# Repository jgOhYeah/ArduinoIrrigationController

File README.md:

# Arduino Irrigation Controller
An irrigation controller for a small farm that remotely controls a set of linear actuators that raise and lower flaps over pipes.
## This is still a WORK IN PROGRESS!
I am mainly using this repository to transfer files! If you are interested in using this, have a look at `SlaveUnit/SlaveUnit3.6` and `Controller/3.4`. **There will be bugs!**
## Links
Most of these notes are very out of date and based off old versions - I have not properly updated the documentation for quite a while!
- [User Guide](Documentation/UserGuide.md)
- [Technical Notes and rambling](Documentation/TechnicalNotes)
# Parts
## Master
- Arduino Mega
- 3 buttons (left, right and select)
- Character lcd (currently using a 40 by 2 lcd, also works on a 16 by 2 lcd by selecting macros and `#defines`, could be modified for a 20 by 4).
## Slaves
- Arduino Uno / Nano / Atmega328p driving a H bridge motor driver to power a linear actuator opening and shutting the bay outlets

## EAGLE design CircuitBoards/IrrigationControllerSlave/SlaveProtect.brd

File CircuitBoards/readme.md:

Please note that these are a work in progress.

The slave circuit and layout is about done, I am waiting to finish the slave design and build several of them to test lots of devices on the bus before I do the master board layout.

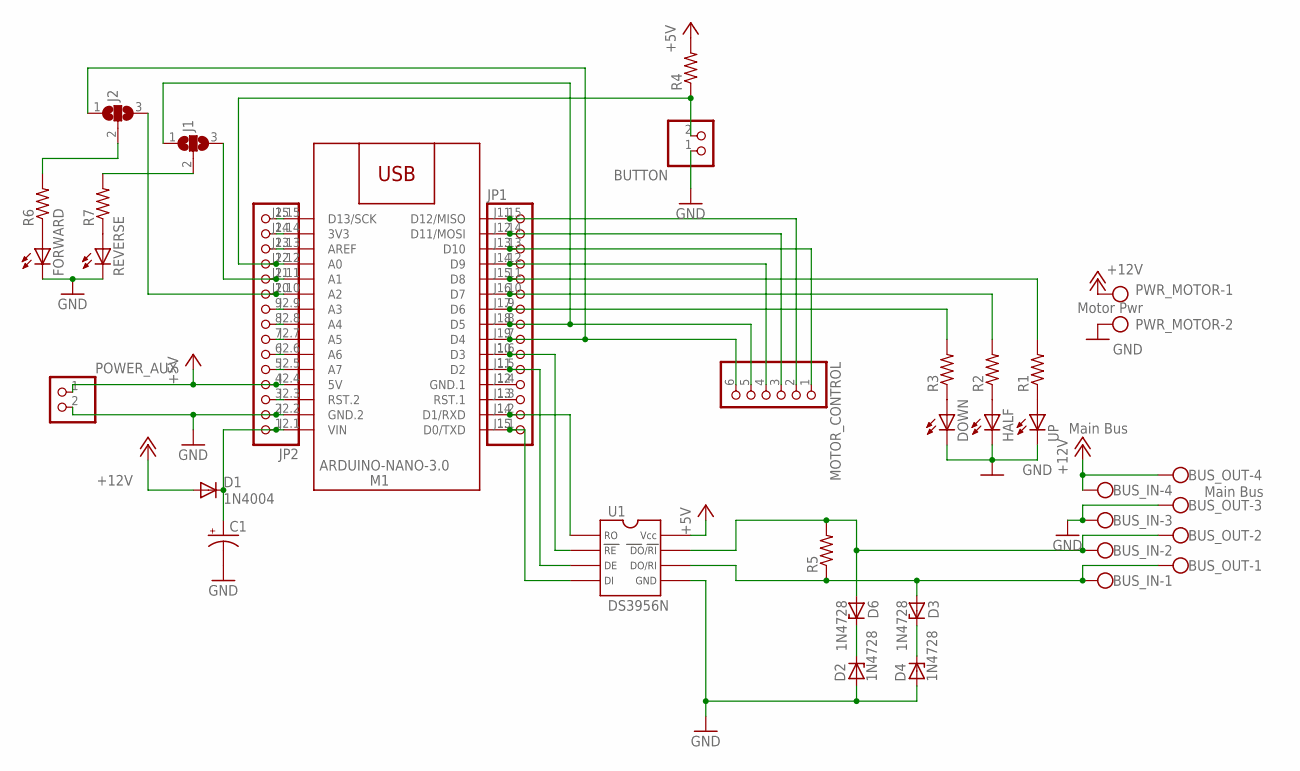
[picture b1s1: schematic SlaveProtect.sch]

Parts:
BUS_IN: Main Bus; W237-4
BUS_OUT: Main Bus; W237-4
BUTTON: PINHD-1X2; 1X02
C1: CPOL-USE3.5-10; E3,5-10
D1: 1N4004; DO41-10
D2, D3, D4, D6: 1N4728; DO41Z10
DOWN: LED5MM
FORWARD: LED5MM
HALF: LED5MM
J1, J2: SJ2W; SJ_2
JP1, JP2: PINHD-1X15-CB; 1X15-CB
M1: ARDUINO-NANO-3.0
MOTOR_CONTROL: PINHD-1X6; 1X06
POWER_AUX: PINHD-1X2; 1X02
PWR_MOTOR: Motor Pwr; W237-102
R1, R2, R3, R4, R5, R6, R7: FLIPFLOP-RES; 0805-THM
REVERSE: LED5MM
U1: DS3956N; DIL08
UP: LED5MM

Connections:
+5V: JP2.4, M1.J2.4 (5V), POWER_AUX.1, R4.2, U1.8 (VCC)
+12V: BUS_IN.4, BUS_OUT.4, D1.A, PWR_MOTOR.1
GND: BUS_IN.3, BUS_OUT.3, BUTTON.1, C1.-, D2.A, D4.A, DOWN.K (C), FORWARD.K (C), HALF.K (C), JP2.2, M1.J2.2 (GND.2), POWER_AUX.2, PWR_MOTOR.2, REVERSE.K (C), U1.5 (GND), UP.K (C)
unnamed: R1.1, UP.A
unnamed: HALF.A, R2.1
unnamed: DOWN.A, R3.1
unnamed: BUTTON.2, JP2.12, M1.J2.12 (A0), R4.1
unnamed: BUS_IN.1, BUS_OUT.1, D3.A, R5.1, U1.6 (DO/RI)
unnamed: BUS_IN.2, BUS_OUT.2, D6.A, R5.2, U1.7 (_DO/RI_)
unnamed: JP1.10, M1.J1.6 (D3), U1.2 (_RE_)
unnamed: JP1.11, M1.J1.5 (D2), U1.3 (DE)
unnamed: JP1.14, M1.J1.2 (D1/RXD), U1.1 (RO)
unnamed: JP1.15, M1.J1.1 (D0/TXD), U1.4 (DI)
unnamed: JP1.7, M1.J1.9 (D6), R3.2
unnamed: JP1.6, M1.J1.10 (D7), R2.2
unnamed: JP1.5, M1.J1.11 (D8), R1.2
unnamed: J1.1, JP1.8, M1.J1.8 (D5), MOTOR_CONTROL.5
unnamed: J1.2, R7.2
unnamed: C1.+, D1.C, JP2.1, M1.J2.1 (VIN)
unnamed: FORWARD.A, R6.1
unnamed: R7.1, REVERSE.A
unnamed: D2.C, D6.C
unnamed: D3.C, D4.C
unnamed: JP2.3, M1.J2.3 (RST.2)
unnamed: JP2.5, M1.J2.5 (A7)
unnamed: JP2.6, M1.J2.6 (A6)
unnamed: JP2.7, M1.J2.7 (A5)
unnamed: JP2.8, M1.J2.8 (A4)
unnamed: JP2.9, M1.J2.9 (A3)
unnamed: J2.3, JP2.10, M1.J2.10 (A2)
unnamed: J1.3, JP2.11, M1.J2.11 (A1)
unnamed: J2.1, JP1.9, M1.J1.7 (D4), MOTOR_CONTROL.6
unnamed: JP2.13, M1.J2.13 (AREF)
unnamed: JP2.14, M1.J2.14 (3V3)
unnamed: JP2.15, M1.J2.15 (D13/SCK)
unnamed: JP1.1, M1.J1.15 (D12/MISO), MOTOR_CONTROL.2
unnamed: JP1.2, M1.J1.14 (D11/MOSI), MOTOR_CONTROL.3
unnamed: JP1.3, M1.J1.13 (D10), MOTOR_CONTROL.1
unnamed: JP1.12, M1.J1.4 (GND.1)
unnamed: JP1.13, M1.J1.3 (RST.1)
unnamed: JP1.4, M1.J1.12 (D9), MOTOR_CONTROL.4
unnamed: J2.2, R6.2

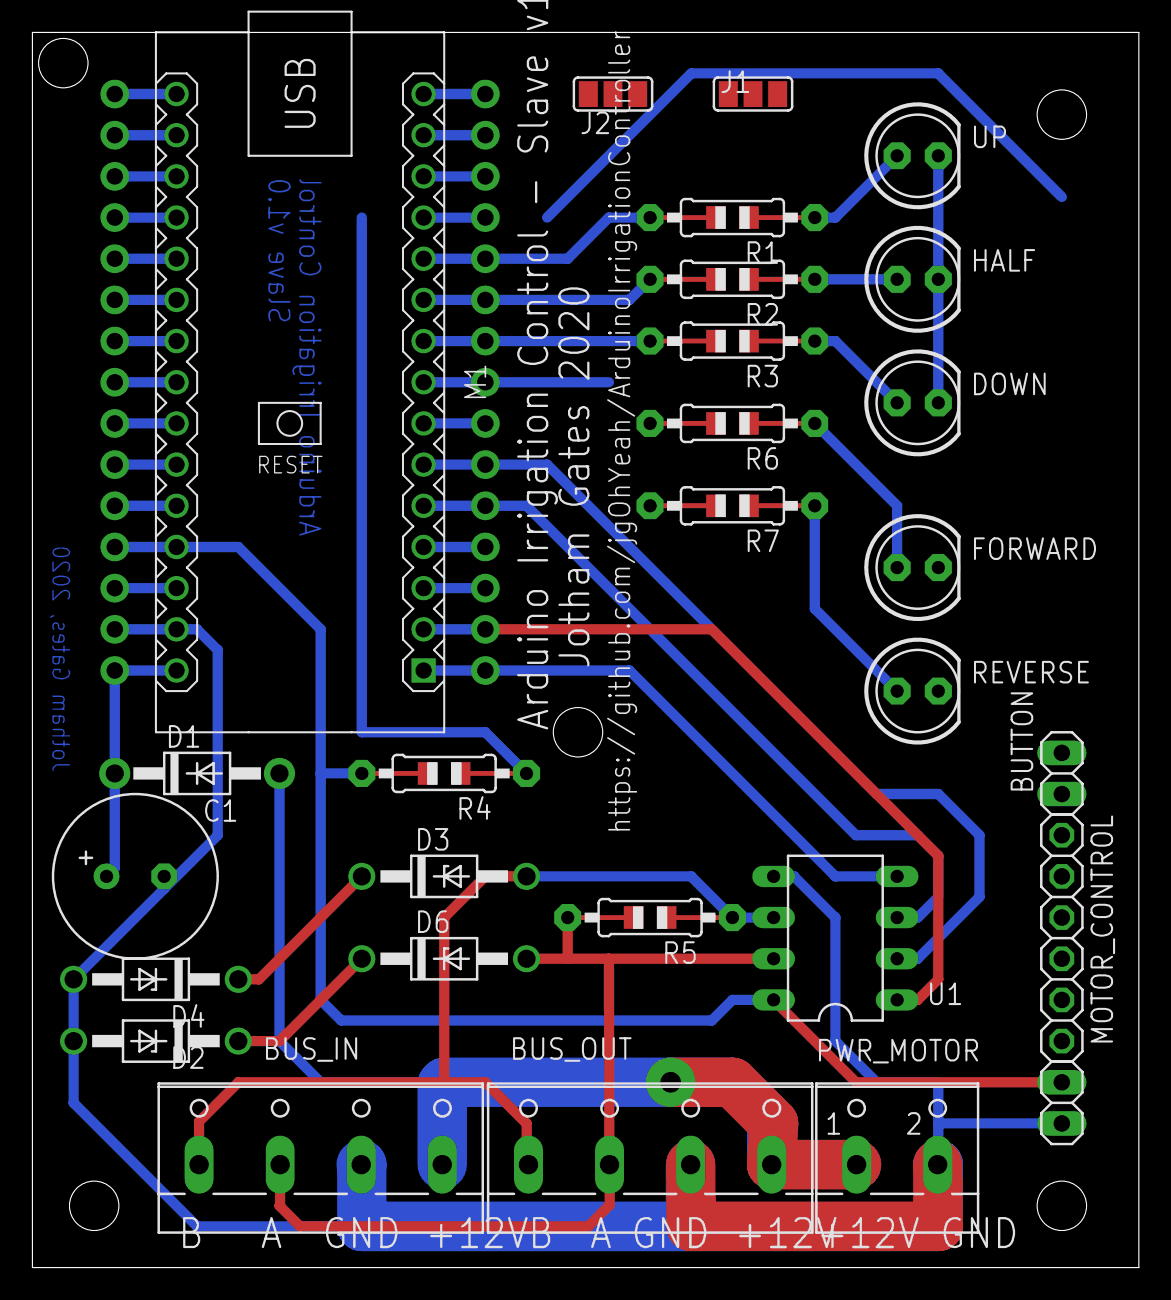
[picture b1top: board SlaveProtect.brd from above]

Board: 2 copper layers, 68.2 x 76.2 mm, 30 parts (0 on the bottom side), 42 nets.

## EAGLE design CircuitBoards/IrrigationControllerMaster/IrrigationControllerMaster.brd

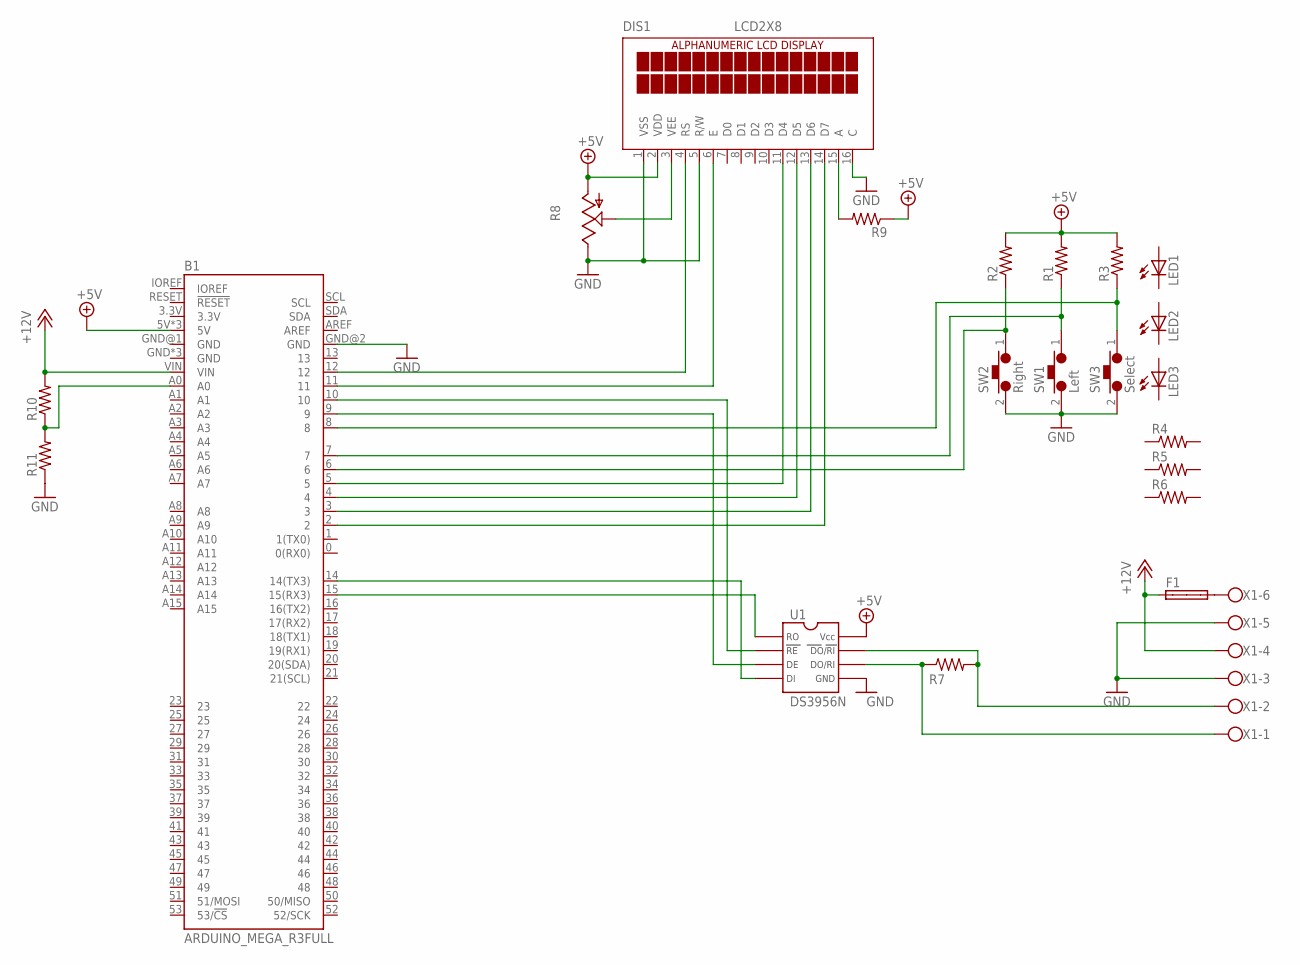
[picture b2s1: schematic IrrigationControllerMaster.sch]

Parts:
B1: ARDUINO_MEGA_R3FULL; ARDUINO_MEGA_NO_SILK
DIS1: LCD2X8; 2X08_JAYCAR
F1: SHK20L
LED1, LED2, LED3: LED5MM
R1, R2, R3, R4, R5, R6, R7, R9, R10, R11: FLIPFLOP-RES; 0805-THM
R8: TRIM_US-ECP10S; ECP10S
SW1: Left; 2PIN
SW2: Right; 2PIN
SW3: Select; 2PIN
U1: DS3956N; DIL08
X1: W237-6

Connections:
+5V: B1.5V, B1.5V@1 (5V), B1.5V@2 (5V), DIS1.2 (VDD), R1.2, R2.2, R3.2, R8.A, R9.1, U1.8 (VCC)
+12V: B1.VIN, F1.1A, R10.2, X1.4
GND: B1.GND@2 (GND), DIS1.1 (VSS), DIS1.5 (R/W), DIS1.16 (C), R8.E, R11.1, SW1.2, SW2.2, SW3.2, U1.5 (GND), X1.3, X1.5
unnamed: R7.2, U1.7 (_DO/RI_), X1.2
unnamed: R7.1, U1.6 (DO/RI), X1.1
unnamed: B1.7, R1.1, SW1.1
unnamed: B1.6, R2.1, SW2.1
unnamed: B1.8, R3.1, SW3.1
unnamed: DIS1.3 (VEE), R8.S
unnamed: B1.12, DIS1.4 (RS)
unnamed: B1.11, DIS1.6 (E)
unnamed: B1.5, DIS1.11 (D4)
unnamed: B1.4, DIS1.12 (D5)
unnamed: B1.3, DIS1.13 (D6)
unnamed: B1.2, DIS1.14 (D7)
unnamed: B1.15 (15(RX3)), U1.1 (RO)
unnamed: B1.14 (14(TX3)), U1.4 (DI)
unnamed: B1.10, U1.2 (_RE_)
unnamed: B1.9, U1.3 (DE)
unnamed: DIS1.15 (A), R9.2
unnamed: B1.A0, R10.1, R11.2
unnamed: F1.2A, X1.6

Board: 2 copper layers, 22 parts (0 on the bottom side), 22 nets, no tracks yet.

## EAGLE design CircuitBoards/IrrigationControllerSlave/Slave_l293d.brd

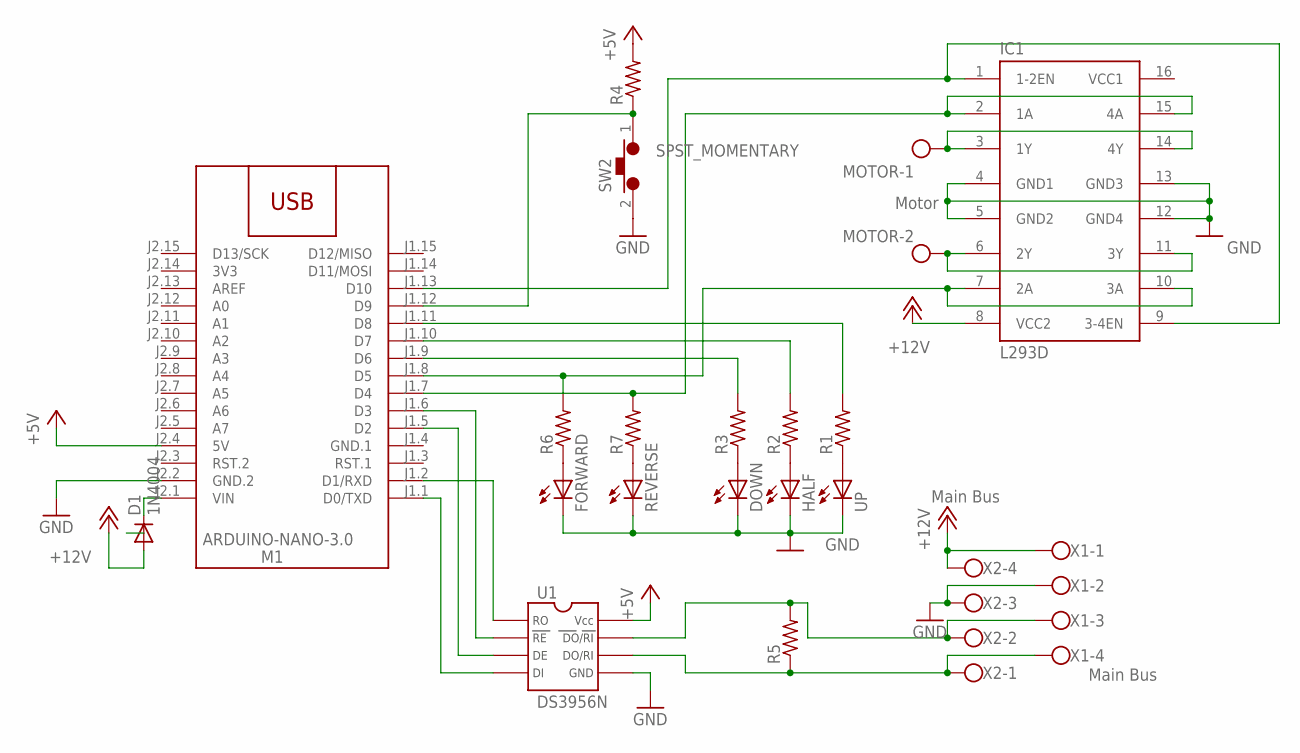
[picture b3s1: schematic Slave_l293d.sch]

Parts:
D1: 1N4004; DO41-10
DOWN: LED5MM
FORWARD: LED5MM
HALF: LED5MM
IC1: L293D; DIL16
M1: ARDUINO-NANO-3.0
MOTOR: Motor; W237-102
R1, R2, R3, R4, R5, R6, R7: FLIPFLOP-RES; 0805-THM
REVERSE: LED5MM
SW2: SPST_MOMENTARY; 2PIN
U1: DS3956N; DIL08
UP: LED5MM
X1, X2: Main Bus; W237-4

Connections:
3V3: M1.J2.14 (3V3)
+5V: M1.J2.4 (5V), R4.2, U1.8 (VCC)
+12V: D1.A, IC1.8 (VCC2), X1.1, X2.4
GND: DOWN.K (C), FORWARD.K (C), HALF.K (C), IC1.4 (GND1), IC1.5 (GND2), IC1.12 (GND4), IC1.13 (GND3), M1.J2.2 (GND.2), REVERSE.K (C), SW2.2, U1.5 (GND), UP.K (C), X1.2, X2.3
GND.1: M1.J1.4 (GND.1)
unnamed: R1.1, UP.A
unnamed: HALF.A, R2.1
unnamed: DOWN.A, R3.1
unnamed: M1.J1.12 (D9), R4.1, SW2.1
unnamed: R5.1, U1.6 (DO/RI), X1.4, X2.1
unnamed: R5.2, U1.7 (_DO/RI_), X1.3, X2.2
unnamed: M1.J1.6 (D3), U1.2 (_RE_)
unnamed: M1.J1.5 (D2), U1.3 (DE)
unnamed: M1.J1.2 (D1/RXD), U1.1 (RO)
unnamed: M1.J1.1 (D0/TXD), U1.4 (DI)
unnamed: M1.J1.9 (D6), R3.2
unnamed: M1.J1.10 (D7), R2.2
unnamed: M1.J1.11 (D8), R1.2
unnamed: D1.C, M1.J2.1 (VIN)
unnamed: FORWARD.A, R6.1
unnamed: R7.1, REVERSE.A
unnamed: IC1.2 (1A), IC1.15 (4A), M1.J1.7 (D4), R7.2
unnamed: IC1.3 (1Y), IC1.14 (4Y), MOTOR.1
unnamed: IC1.1 (1-2EN), IC1.9 (3-4EN), M1.J1.13 (D10)
unnamed: IC1.6 (2Y), IC1.11 (3Y), MOTOR.2
unnamed: IC1.7 (2A), IC1.10 (3A), M1.J1.8 (D5), R6.2
VCC1: IC1.16 (VCC1)

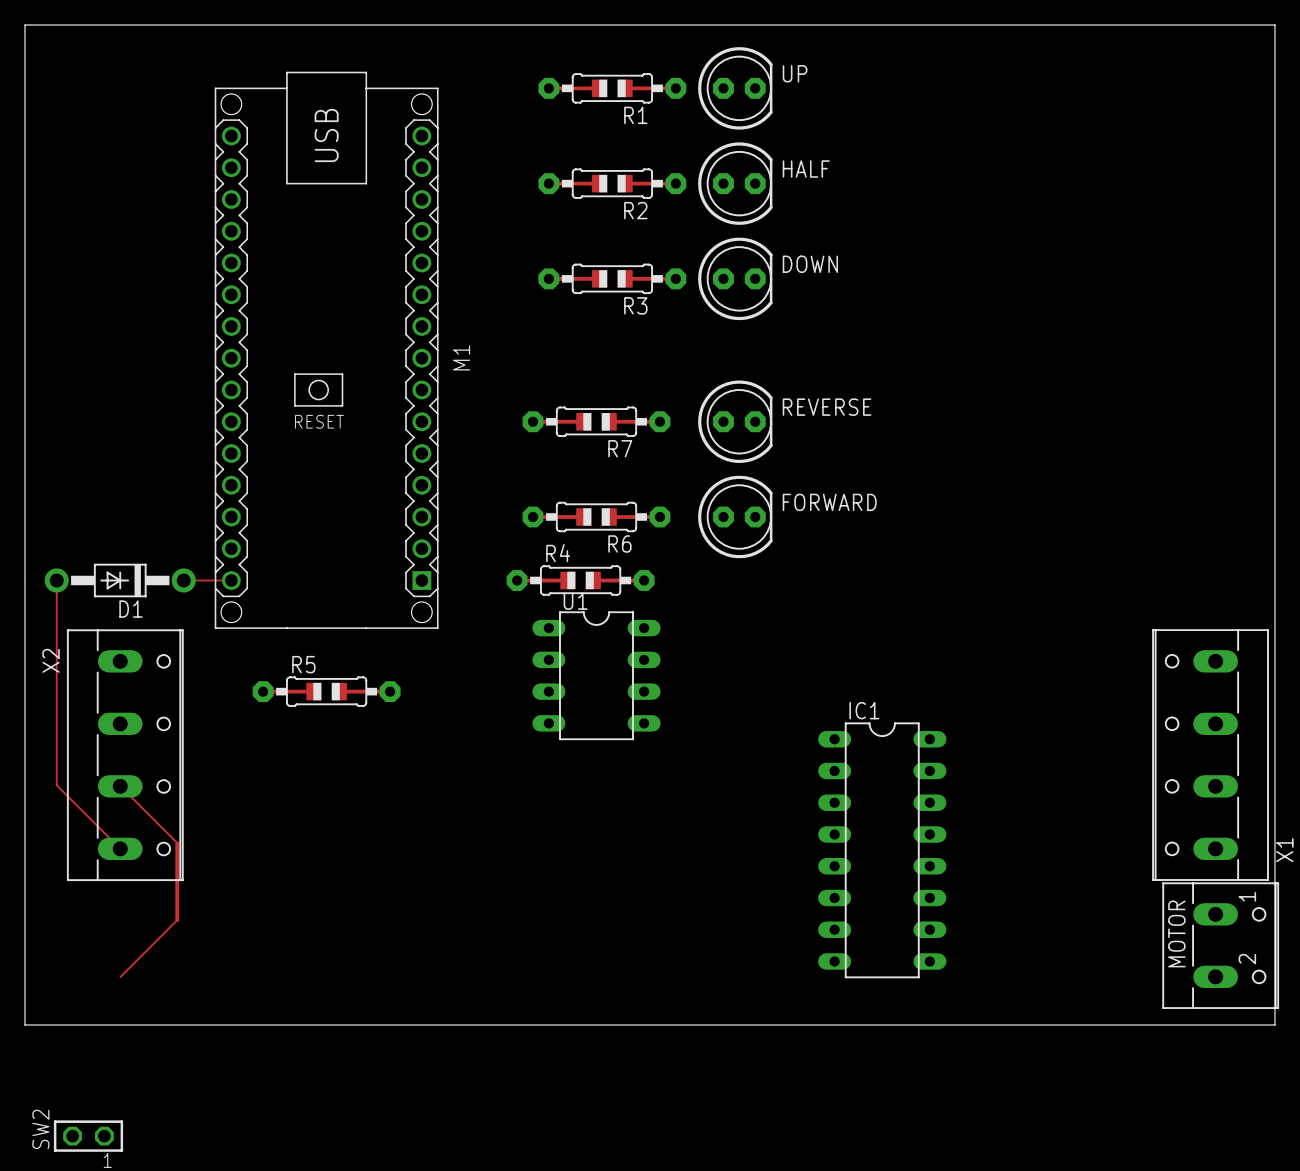
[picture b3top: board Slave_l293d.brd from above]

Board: 2 copper layers, 100.0 x 80.0 mm, 20 parts (0 on the bottom side), 24 nets.

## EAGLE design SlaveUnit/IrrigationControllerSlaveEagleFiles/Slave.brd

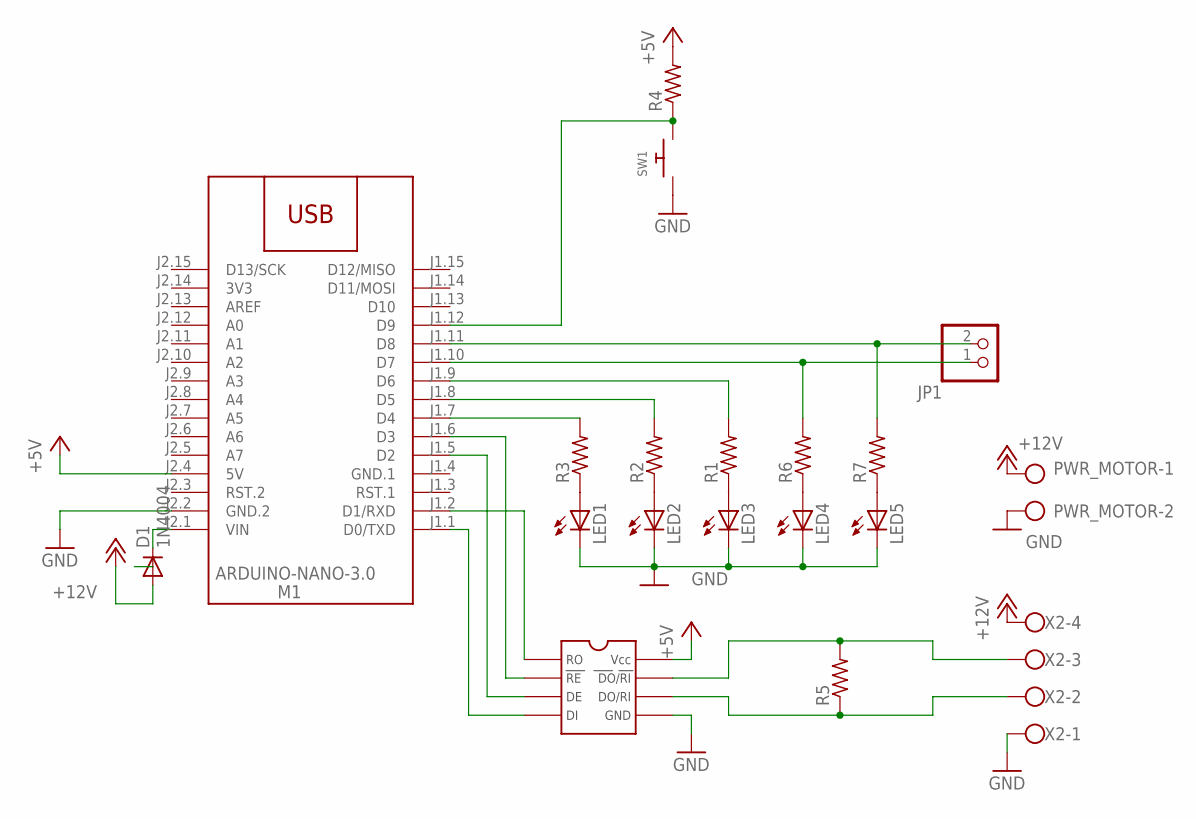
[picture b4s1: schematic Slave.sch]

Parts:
D1: 1N4004; DO41-10
JP1: PINHD-1X2; 1X02
LED1, LED2, LED3, LED4, LED5: LED5MM
M1: ARDUINO-NANO-3.0
PWR_MOTOR: W237-102
R1, R2, R3, R4, R5, R6, R7: FLIPFLOP-RES; 0805-THM
SW1: SWITCH_PUSHBUTTONEVQ-PE; TACT_PANA-EVQ
U1: DS3956N; DIL08
X2: W237-4

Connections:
3V3: M1.J2.14 (3V3)
+5V: M1.J2.4 (5V), R4.2, U1.8 (VCC)
+12V: D1.A, PWR_MOTOR.1, X2.4
GND: LED1.K (C), LED2.K (C), LED3.K (C), LED4.K (C), LED5.K (C), M1.J2.2 (GND.2), PWR_MOTOR.2, SW1.P$1, U1.5 (GND), X2.1
GND.1: M1.J1.4 (GND.1)
unnamed: LED3.A, R1.1
unnamed: LED2.A, R2.1
unnamed: LED1.A, R3.1
unnamed: M1.J1.12 (D9), R4.1, SW1.P$2
unnamed: R5.1, U1.6 (DO/RI), X2.2
unnamed: R5.2, U1.7 (_DO/RI_), X2.3
unnamed: M1.J1.6 (D3), U1.2 (_RE_)
unnamed: M1.J1.5 (D2), U1.3 (DE)
unnamed: M1.J1.2 (D1/RXD), U1.1 (RO)
unnamed: M1.J1.1 (D0/TXD), U1.4 (DI)
unnamed: M1.J1.7 (D4), R3.2
unnamed: M1.J1.8 (D5), R2.2
unnamed: M1.J1.9 (D6), R1.2
unnamed: JP1.2, M1.J1.11 (D8), R7.2
unnamed: JP1.1, M1.J1.10 (D7), R6.2
unnamed: D1.C, M1.J2.1 (VIN)
unnamed: LED4.A, R6.1
unnamed: LED5.A, R7.1

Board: 2 copper layers, 19 parts (0 on the bottom side), 21 nets, no tracks yet.

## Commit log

2018-09-15 Originl Code
2018-09-16 Started Converting to use PJON
2018-09-17 Still integrating stuff
2018-09-18 Added svgs of screen
2018-09-18 Still says 160
2018-10-03 Still working on it
2018-10-04 Still Working
2018-11-05 Added baud rate settings
2018-11-06 MelbourneCupWeekend, Fixed Crashes on master and started to add featurs to the slave.
    Also started to break defines.h into smaller files.
    Still to do: read/set EEPROM over PJON
    Flashing leds on the slave.
    EEPROM read/set on the master
    lorawan transiever on master to allow remotes to communicate?
2018-11-07 Added but not tested reading and writing to eeprom over PJON
2018-11-08 Started to add eeprom editor to controller.
    Use the second latest dated code for the controller for the most stable
2018-11-11 UpdateVersion, start to add remote setting of eeprom values to the up time
2018-11-16 Starting to add features to the library
2018-11-16 Started to add more usable buttons to set slave's eeprom settings. - Look at _NOTES.ino in the controller files for more info
2018-11-18 Improved error codes, bug fixes
2018-12-02 Added software version for slave
2018-12-03 swapping computers - flashing .eds
2018-12-03 Still flashing LEDs - not much extra
2018-12-05 Still working on flashing leds and callback functions
2018-12-06 CallbacksWorking
2018-12-07 CallbackLibraryShould be working - hAVE NOT YET TESTED
    Also started a new version of the slave unit because so much will need to be changed to use the new library
2018-12-07 hALFWAY_tHROUGH_FIXING_#DEFINES
2018-12-09 DONE_FIXING_NAMING_CONVENTIONS_IN_SLAVE_3.6, Adding in led and callback libraries - minor changes to wording in callback library
2018-12-10 Adding to flashing leds
2018-12-28 Added Debug to callback library and fixed passing defines to it.
2018-12-29 Fixed callback overloads and issues, improved debugging for each part with macros
2019-01-03 Fixing eeprom settings and naming conventions in controller
2019-01-04 Updates, Master now uses callback library, bug fixes
2019-01-04 Started dding macros for 40 by 2 lcd or 16 by 2 lcd.
2019-01-14 Bug fixes, a bit of modifying for different displays
2019-01-22 Partway through settings cli parse update
2020-05-13 Added schematics and slave board layout

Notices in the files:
parts and their libraries:
SparkFun-Boards: Licensing: Creative Commons ShareAlike 4.0 International - https://creativecommons.org/licenses/by-sa/4.0
diy-modules: Released under the Creative Commons Attribution 4.0 International License: http://creativecommons.org/licenses/by/4.0
